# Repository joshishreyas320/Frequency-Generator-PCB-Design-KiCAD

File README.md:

# DDS Frequency Generator

> KiCad PCB Design | 2-Layer Board | AD9833 + ATmega328A

---

## Project Description
A Direct Digital Synthesis (DDS) frequency generator PCB designed using **KiCad**. The board uses the **AD9833BRMZ** DDS IC controlled by an **ATmega328A** microcontroller over SPI to generate sine, triangle, and square waveforms. A **24MHz CFPS-72 reference oscillator** provides precise clocking, and an **LM318M high-speed op-amp** conditions the output signal for a coaxial connector.

**Short Description (≤350 chars):**
> DDS-based frequency generator PCB using AD9833 + ATmega328A. Generates sine/triangle/square waves controlled via SPI. Includes LM318M output amplifier, 24MHz reference oscillator, and coaxial output. Designed in KiCad.

---

## Key Components

| Component | Description |
|-----------|-------------|
| **AD9833BRMZ-REEL** | DDS waveform generator – sine/triangle/square via SPI |
| **ATmega328-A** | MCU controller for AD9833 frequency register writes |
| **CFPS-72 24MHz** | Precision crystal oscillator – DDS reference clock |
| **LM318M** | High-speed op-amp for output signal amplification |
| **AMS1117-5.0** | 5V LDO regulator |
| **Potentiometers (2x)** | Frequency and amplitude adjustment |
| **SW_SPDT** | Waveform selection switch |
| **Coaxial Connector** | RF signal output |

---

## Design Features
- AD9833 generates sine, triangle, and square waveforms digitally
- ATmega328A programs AD9833 frequency/phase registers over SPI
- CFPS-72 24MHz reference oscillator provides stable DDS clock
- LM318M op-amp output stage for signal conditioning and drive
- Dual ±12V supply for op-amp headroom
- Potentiometers allow analog frequency fine-tuning

---

## Signal Flow
```
ATmega328A – MCU Controller
       ↓ SPI (MOSI/CLK/CS)
  AD9833 – DDS Waveform Generator
       ↓
  LM318M – Output Amplifier
       ↓
  Waveform Select Switch (SW_SPDT)
       ↓
  Coaxial Output Connector
       ↑
  AMS1117-5.0 ← 5V Supply
  ±12V Supply ← Dual Rail Power Input
```

---

## Files Included
- Frequency_Generator_A.kicad_sch – Schematic
- Frequency_Generator_A.kicad_pcb – PCB Layout
- Frequency_Generator_A-backups/ – Auto-backup files

---

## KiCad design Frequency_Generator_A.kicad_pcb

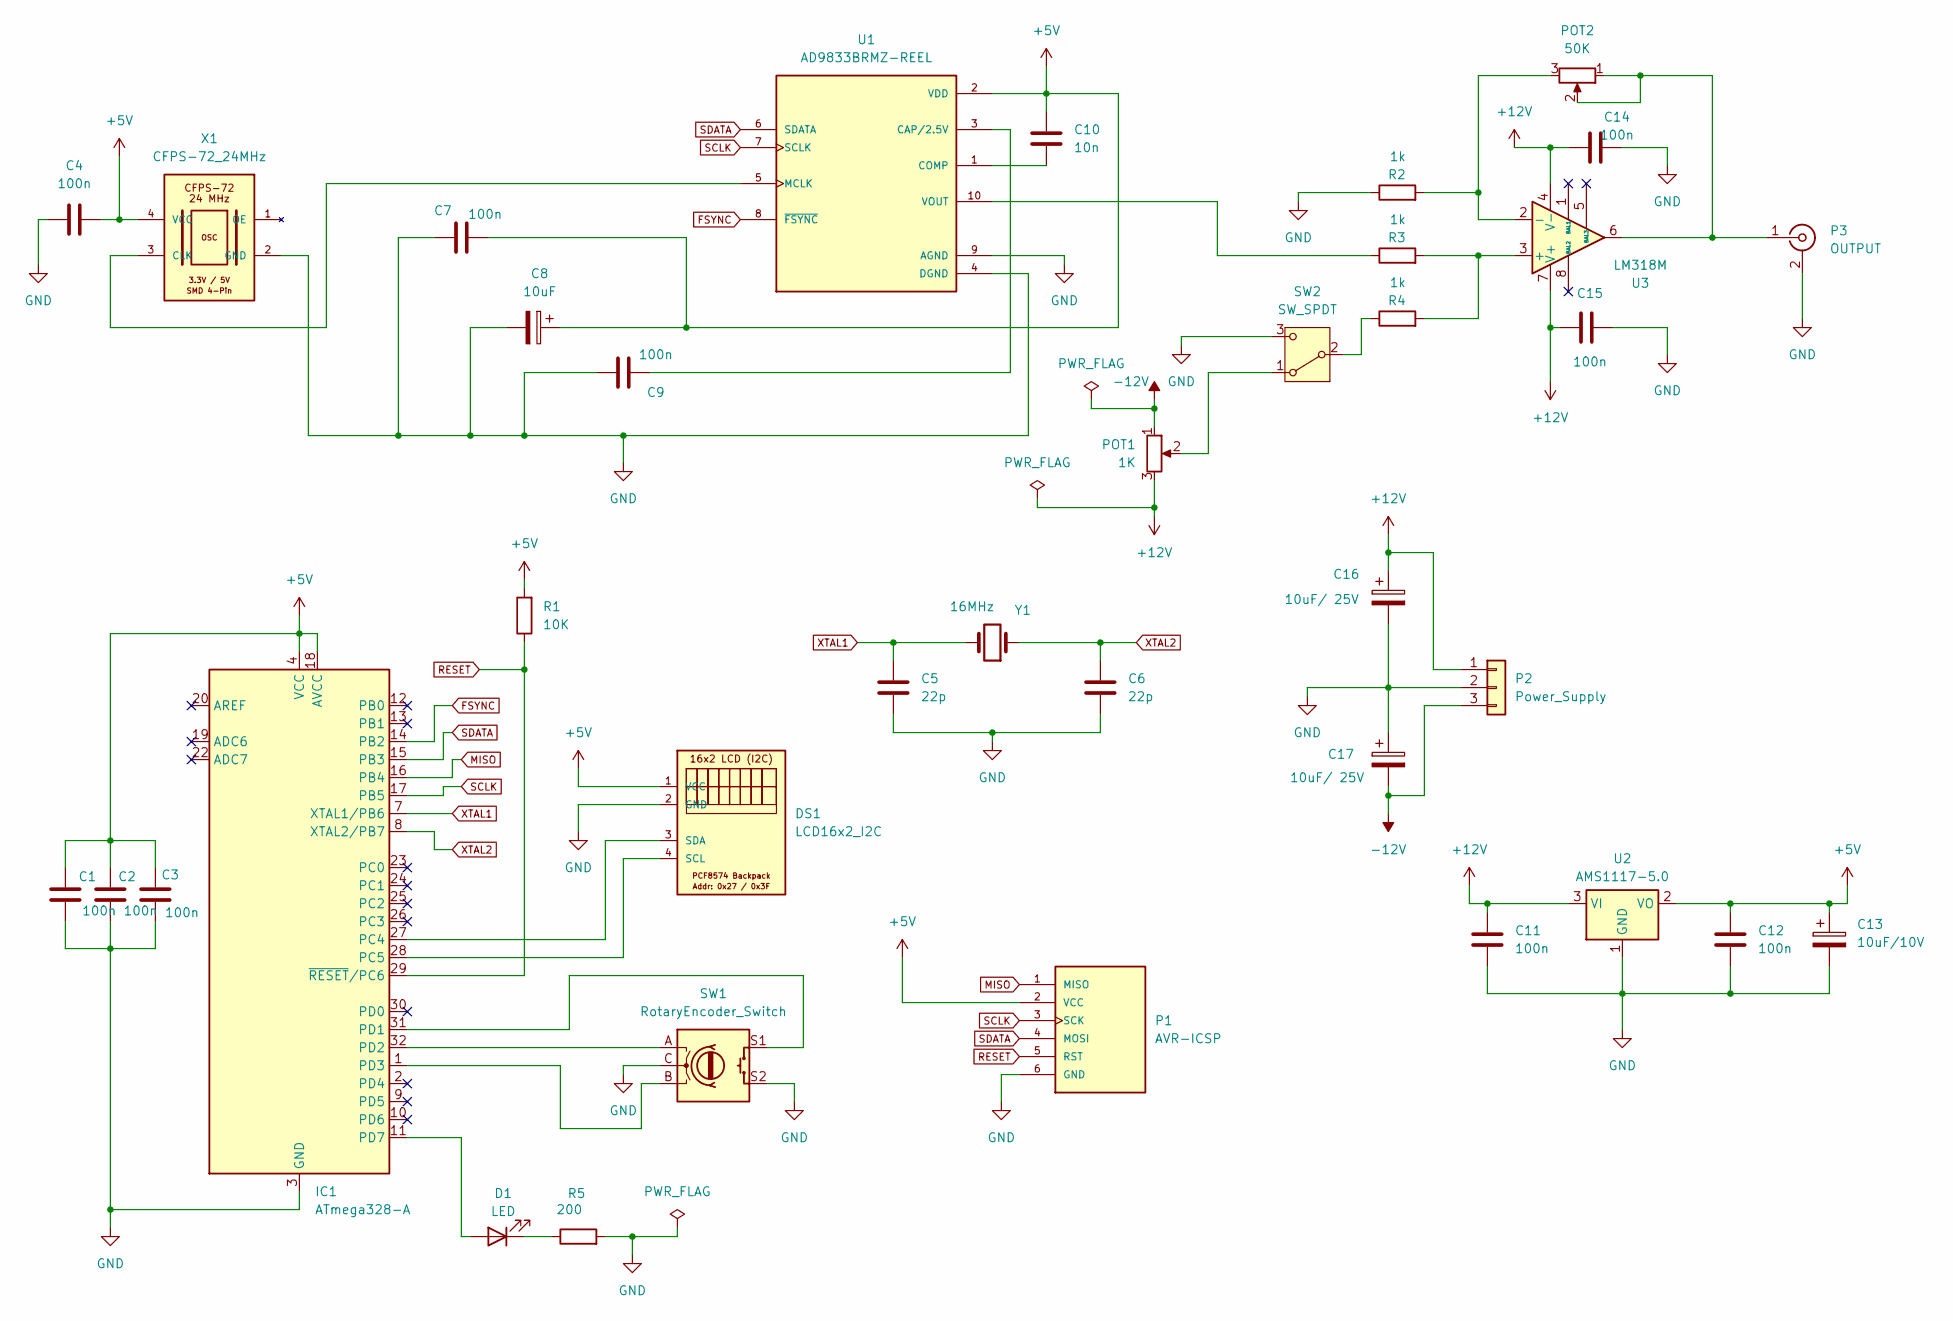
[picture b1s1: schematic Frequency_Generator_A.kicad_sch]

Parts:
C1, C2, C3, C4, C7, C9, C11, C12, C14, C15: 100n; C_0805_2012Metric
C5, C6: 22p; C_0805_2012Metric
C8: 10uF; CP_Elec_5x5.3
C10: 10n; C_0805_2012Metric
C13: 10uF/10V; CP_Elec_5x5.3
C16, C17: 10uF/ 25V; CP_Elec_6.3x5.3
D1: LED; LED_D5.0mm
DS1: LCD16x2_I2C; PinHeader_1x16_P2.54mm_Vertical
IC1: ATmega328-A; TQFP-32_7x7mm_P0.8mm
P1: AVR-ICSP; PinHeader_2x03_P2.54mm_Vertical
P2: Power_Supply; BarrelJack_Horizontal
P3: OUTPUT; PinHeader_1x03_P2.54mm_Vertical
POT1: 1K; Potentiometer_Piher_PT-6-V_Vertical
POT2: 50K; Potentiometer_Piher_PT-6-V_Vertical
R1: 10K; R_0805_2012Metric
R2, R3, R4: 1k; R_0805_2012Metric
R5: 200; R_0805_2012Metric
SW1: RotaryEncoder_Switch; RotaryEncoder_Alps_EC11E-Switch_Vertical_H20mm
SW2: SW_SPDT; SW_CK_JS202011AQN_DPDT_Angled
U1: AD9833BRMZ-REEL; MSOP-10_3x3mm_P0.5mm; PARTREV G
U2: AMS1117-5.0; SOT-223-3_TabPin2
U3: LM318M; SOIC-8_3.9x4.9mm_P1.27mm
X1: CFPS-72_24MHz; Oscillator_SMD_Abracon_ASE-4Pin_3.2x2.5mm; MPN CFPS-72
Y1: 16MHz; Crystal_HC49-U_Vertical

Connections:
+5V: C1.1, C2.1, C3.1, C4.2, C7.2, C8.1, C10.1, C12.1, C13.1, DS1.1 (VCC), IC1.4 (VCC), IC1.6 (VCC), IC1.18 (AVCC), P1.2 (VCC), R1.2, U1.2 (VDD), U2.2 (VO), X1.4 (VCC)
+12V: C11.1, C14.1, C15.1, C16.1, P2.1, POT1.3, U2.3 (VI), U3.4 (V-), U3.7 (V+)
-12V: C17.2, P2.3, POT1.1
FSYNC: IC1.14 (PB2), U1.8 (~FSYNC)
GND: C1.2, C2.2, C3.2, C4.1, C5.2, C6.1, C7.1, C8.2, C9.2, C11.2, C12.2, C13.2, C14.2, C15.2, C16.2, C17.1, DS1.2 (GND), IC1.3 (GND), IC1.5 (GND), IC1.21 (GND), P1.6 (GND), P2.2, P3.2 (Ext), R2.1, R5.2, SW1.C, SW1.S2, SW2.3 (C), U1.4 (DGND), U1.9 (AGND), U2.1 (GND), X1.2 (GND)
MISO: IC1.16 (PB4), P1.1 (MISO)
unnamed: D1.2 (A), IC1.11 (PD7)
unnamed: D1.1 (K), R5.1
unnamed: DS1.4 (SCL), IC1.28 (PC5)
unnamed: DS1.3 (SDA), IC1.27 (PC4)
unnamed: IC1.31 (PD1), SW1.S1
unnamed: IC1.32 (PD2), SW1.A
unnamed: IC1.1 (PD3), SW1.B
unnamed: P3.1 (In), POT2.1, POT2.2, U3.6
unnamed: POT1.2, SW2.1 (A)
unnamed: R4.1, SW2.2 (B)
unnamed: C9.1, U1.3 (CAP/2.5V)
unnamed: C10.2, U1.1 (COMP)
unnamed: U1.5 (MCLK), X1.3 (CLK)
unnamed: R3.1, U1.10 (VOUT)
unnamed: R3.2, R4.2, U3.3 (+)
unnamed: POT2.3, R2.2, U3.2 (-)
RESET: IC1.29 (~RESET/PC6), P1.5 (RST), R1.1
SCLK: IC1.17 (PB5), P1.3 (SCK), U1.7 (SCLK)
SDATA: IC1.15 (PB3), P1.4 (MOSI), U1.6 (SDATA)
XTAL1: C5.1, IC1.7 (XTAL1/PB6), Y1.2
XTAL2: C6.2, IC1.8 (XTAL2/PB7), Y1.1

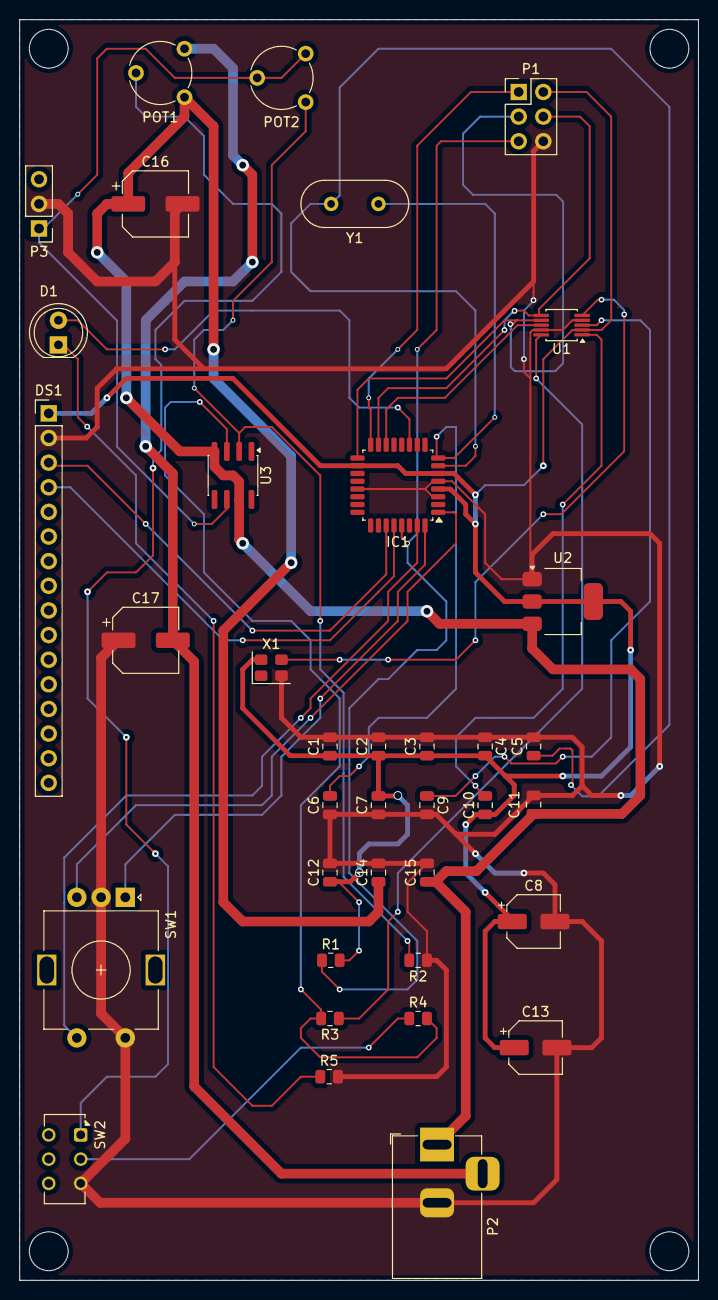
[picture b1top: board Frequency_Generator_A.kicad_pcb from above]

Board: 2 copper layers, 70.0 x 130.0 mm, 37 parts (0 on the bottom side), 27 nets.

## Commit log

2026-06-06 Revise README.md for DDS Frequency Generator project
    Updated project description, key components, design features, signal flow, and included files sections in README.md.
